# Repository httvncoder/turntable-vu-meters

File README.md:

# Turntable VU meters

This is a schematic and PCB I've designed for stereo LED VU meter bars to be mounted in my turntable. It is based around the logarithmic variant of the LM3914, the LM3915, which thus works well for audio.

The LEDs are in a common anode configuration, which is connected to the rightmost pin of each wide connector.

The cathodes are connected to all the other pins of the connectors. The leftmost pin is the LED corresponding to the lowest volume, and the rightmost - 1 for peak volume.

The peak LED also has a small circuit to make it act as an actual peak indicator. This is accomplished with a capacitor.

The circuit is designed for ~12V input voltage, connected on the left connector. GND on top, +12V on bottom.

The bottom connector is for audio input, Left and right. It assumes the audio source shares the GND with the power source.

See the [blog post](http://michd.me/blog/turntable-vu-meters/) for more details on the build process and a bunch of photos.

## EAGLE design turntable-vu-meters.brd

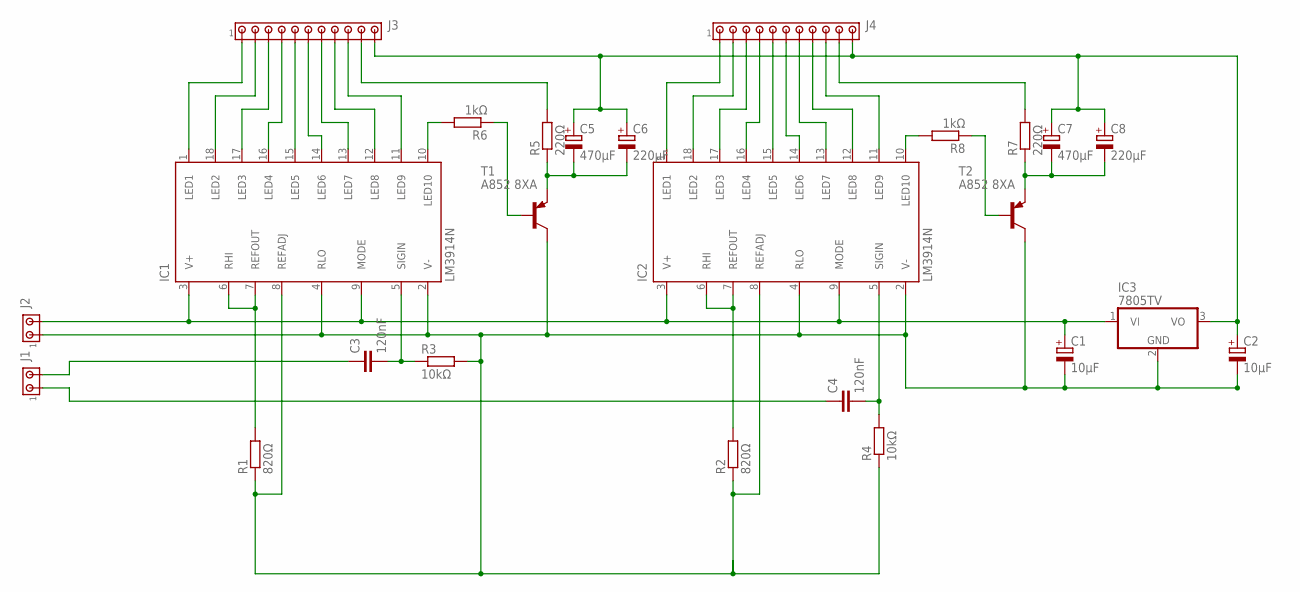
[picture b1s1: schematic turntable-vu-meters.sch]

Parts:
C1, C2: 10μF; E5-6
C3, C4: 120nF; C075-052X106
C5, C7: 470µF; E3,5-8
C6, C8: 220µF; E2,5-7
IC1, IC2: LM3914N; DIL18
IC3: 7805TV; TO220V
J1, J2: MTA02-156; 1X2MTA
J3, J4: MTA11-156; 1X11MTA
R1, R2: 820Ω; 0204/7
R3, R4: 10kΩ; 0204/7
R5, R7: 220Ω; 0204/7
R6, R8: 1kΩ; 0204/7
T1, T2: A852 8XA; TO92

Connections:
unnamed: IC2.17 (LED3), J4.3
unnamed: IC1.18 (LED2), J3.2
unnamed: IC1.1 (LED1), J3.1
unnamed: IC2.16 (LED4), J4.4
unnamed: IC2.15 (LED5), J4.5
unnamed: J3.10, R5.2
unnamed: IC1.11 (LED9), J3.9
unnamed: IC1.12 (LED8), J3.8
unnamed: IC1.13 (LED7), J3.7
unnamed: IC1.14 (LED6), J3.6
unnamed: IC2.1 (LED1), J4.1
unnamed: IC2.18 (LED2), J4.2
unnamed: C1.+, IC1.3 (V+), IC1.9 (MODE), IC2.3 (V+), IC2.9 (MODE), IC3.1 (VI), J2.2
unnamed: J4.10, R7.2
unnamed: IC2.11 (LED9), J4.9
unnamed: C5.-, C6.-, R5.1, T1.1 (E)
unnamed: IC2.14 (LED6), J4.6
unnamed: IC1.10 (LED10), R6.2
unnamed: C3.2, IC1.5 (SIGIN), R3.1
unnamed: C4.2, IC2.5 (SIGIN), R4.2
unnamed: IC1.6 (RHI), IC1.7 (REFOUT), R1.2
unnamed: IC2.6 (RHI), IC2.7 (REFOUT), R2.2
unnamed: IC2.13 (LED7), J4.7
unnamed: IC2.12 (LED8), J4.8
unnamed: C4.1, J1.1
unnamed: C3.1, J1.2
unnamed: R6.1, T1.2 (B)
unnamed: C2.+, C5.+, C6.+, C7.+, C8.+, IC3.3 (VO), J3.11, J4.11
unnamed: IC2.10 (LED10), R8.2
unnamed: R8.1, T2.2 (B)
unnamed: C7.-, C8.-, R7.1, T2.1 (E)
unnamed: C1.-, C2.-, IC1.2 (V-), IC1.4 (RLO), IC1.8 (REFADJ), IC2.2 (V-), IC2.4 (RLO), IC2.8 (REFADJ), IC3.2 (GND), J2.1, R1.1, R2.1, R3.2, R4.1, T1.3 (C), T2.3 (C)
unnamed: IC1.17 (LED3), J3.3
unnamed: IC1.16 (LED4), J3.4
unnamed: IC1.15 (LED5), J3.5

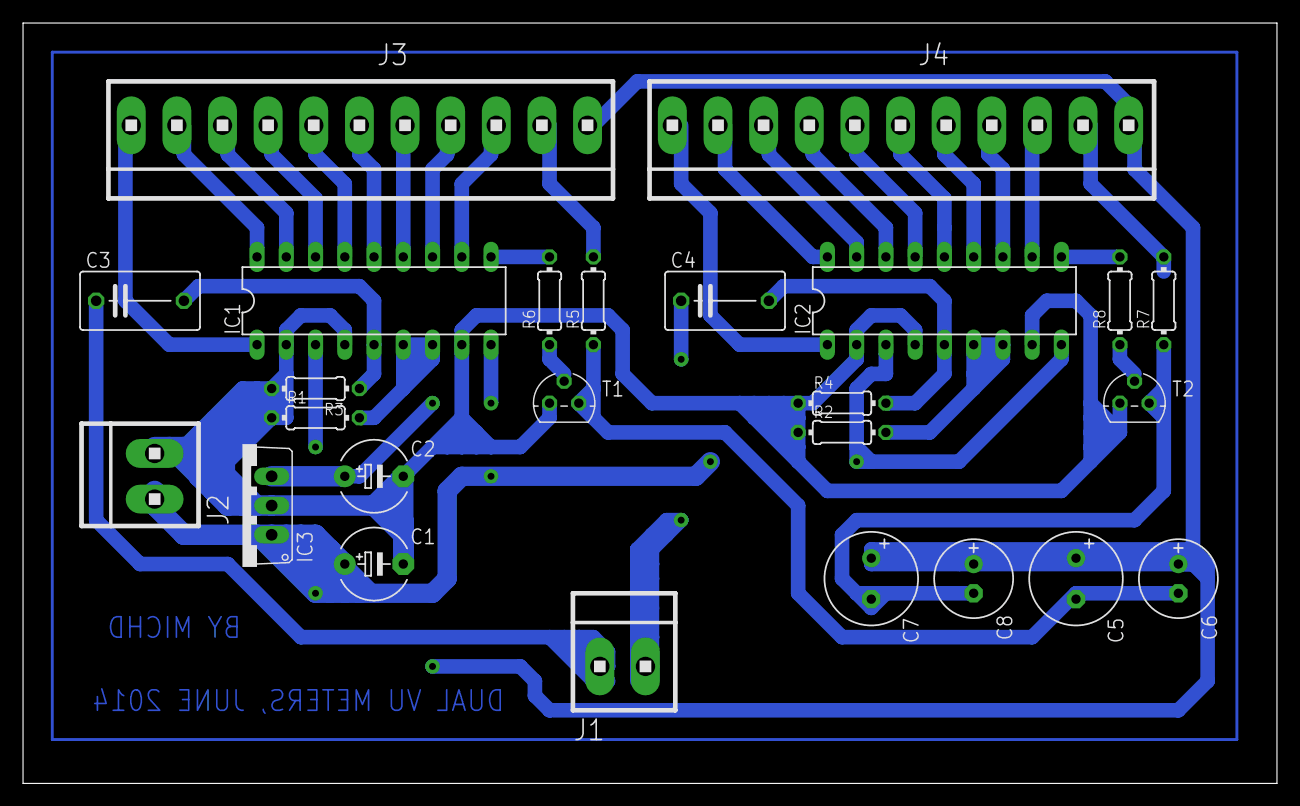
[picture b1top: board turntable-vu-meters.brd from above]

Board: 2 copper layers, 108.9 x 66.0 mm, 25 parts (0 on the bottom side), 35 nets.

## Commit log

2014-06-25 Initial commit, Including finished schematic
2014-06-28 Finish up schematic, add values for components
2014-06-28 Swap connectors
2014-07-06 Finalize schematic and pcb
2014-07-06 Add Readme
2014-07-06 Add license
2014-07-06 Add blog post url to readme
